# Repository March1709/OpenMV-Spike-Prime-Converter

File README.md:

# OpenMV-Spike-Prime-Converter

This project includes a circuit board, mounting accessories, and sample programs that enable OpenMV to be used with LEGO SPIKE Prime by attaching the board to the ultrasonic sensor housing.

The hardware is released as open-source hardware under the Creative Commons Attribution-ShareAlike 4.0 International (CC BY-SA 4.0) license.

- [Open Source Hardware Definition](https://www.oshwa.org/definition/)
- [CC BY-SA 4.0 License](https://creativecommons.org/licenses/by-sa/4.0/)

## File Descriptions

### Hardware

- **board.brd**: An EAGLE-compatible PCB layout file.
- **schematic.sch**: An EAGLE-compatible schematic file.
- **spacer_FRONT**: A spacer used on the front side of the PCB. Insert its protrusions into the outer holes of the PCB, then fix the assembly using the screws that originally held the ultrasonic sensor module in place.
- **spacer_BACK**: A spacer used on the back side of the PCB. Insert its protrusions into the inner holes of the PCB to set the proper distance between the PCB and the ultrasonic sensor housing.

### Sample Programs

- **OpenMV_sample.py**: Sends the number `100` from OpenMV to SPIKE Prime once per second.
- **SPIKE_sample.llsp**: Displays the data received by SPIKE Prime in the console.

## Assembly Instructions

Refer to `mount_example.step` for an example of the assembled hardware.

## License

The hardware design files and mounting accessories are licensed under the Creative Commons Attribution-ShareAlike 4.0 International (CC BY-SA 4.0) license.

- [CC BY-SA 4.0 License](https://creativecommons.org/licenses/by-sa/4.0/)

## Questions and Issues

If you have any questions or encounter any problems, please open an issue in the GitHub Issues section.

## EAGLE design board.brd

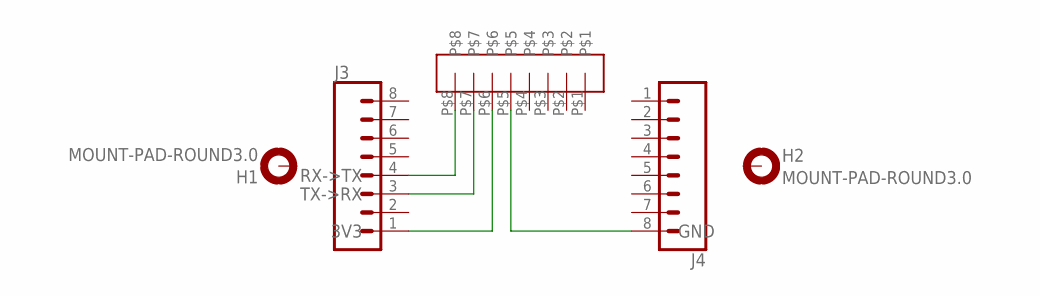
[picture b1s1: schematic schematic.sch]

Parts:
H1, H2: MOUNT-PAD-ROUND3.0; 3,0-PAD
J3, J4: CONN_08"; 1X08
U$1: 1X08

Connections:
3V3: J3.1, U$1.P$6
GND: J4.8, U$1.P$5
RX->TX: J3.4, U$1.P$8
TX->RX: J3.3, U$1.P$7

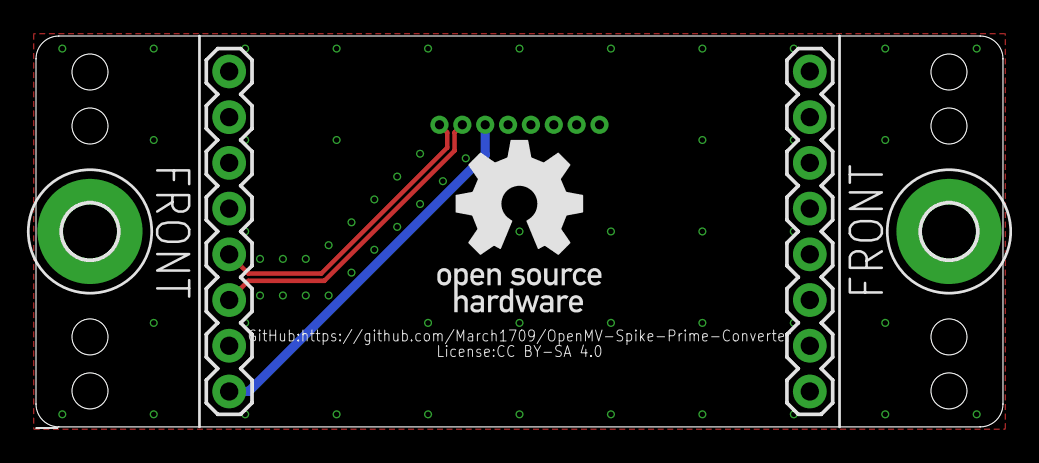
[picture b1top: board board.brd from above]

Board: 2 copper layers, 53.7 x 21.7 mm, 5 parts (1 on the bottom side), 4 nets.

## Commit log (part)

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2023-06-12 Create path
2023-06-12 Create a

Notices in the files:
parts and their libraries:
SparkFun-Connectors: Licensing: Creative Commons ShareAlike 4.0 International - https://creativecommons.org/licenses/by-sa/4.0
